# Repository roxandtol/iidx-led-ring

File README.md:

# Rough plans

> [!WARNING]  
> This would be necessary only if you plan on running encrypted or want to make your cab look *really* cool. otherwise, use 🏳️‍⚧️DJ 

So, the iidx lightning cab has enough lights to make a normal person blind, and as we all know, a legacy cab only has a fraction of them, and they're either neons or plain rgb, meanwhile the lightning cab uses mainly the ws2812b led chip for all the rgb stuff (except the turntables and the subwoofer leds, where they use plain rgb).

So to get some of the lightning leds to a legacy cab, we could switch out the neons on the header with some led boards or led strips from aliexpress, since they follow this pattern

In the manual, there's a white tape led section, which we could link the tape leds to the original spotlights the cab has, and 4 argb led sections which correspond to the gray areas on this picture

So we could use some trickery, and try to make some boards to fit in a legacy cab. The solution I was thinking of is this. where the red circles represent a neon, and the green lines represent the sides in a lightning cab. the red circles would have 27 leds each one (since there's 54 per side), and the sides would have 11 leds (to represent the title box leds). This would work for a 1st - 2nd gen cab. Tricoro cabs have a led strip at the top, which would need a simple led strip

Maybe there could be a led board that uses the original holes of a cab, and looks legit enough, and then a diffuser to not make it as bright (although being honest, I think most people will just turn on concentration mode on their cab lol)

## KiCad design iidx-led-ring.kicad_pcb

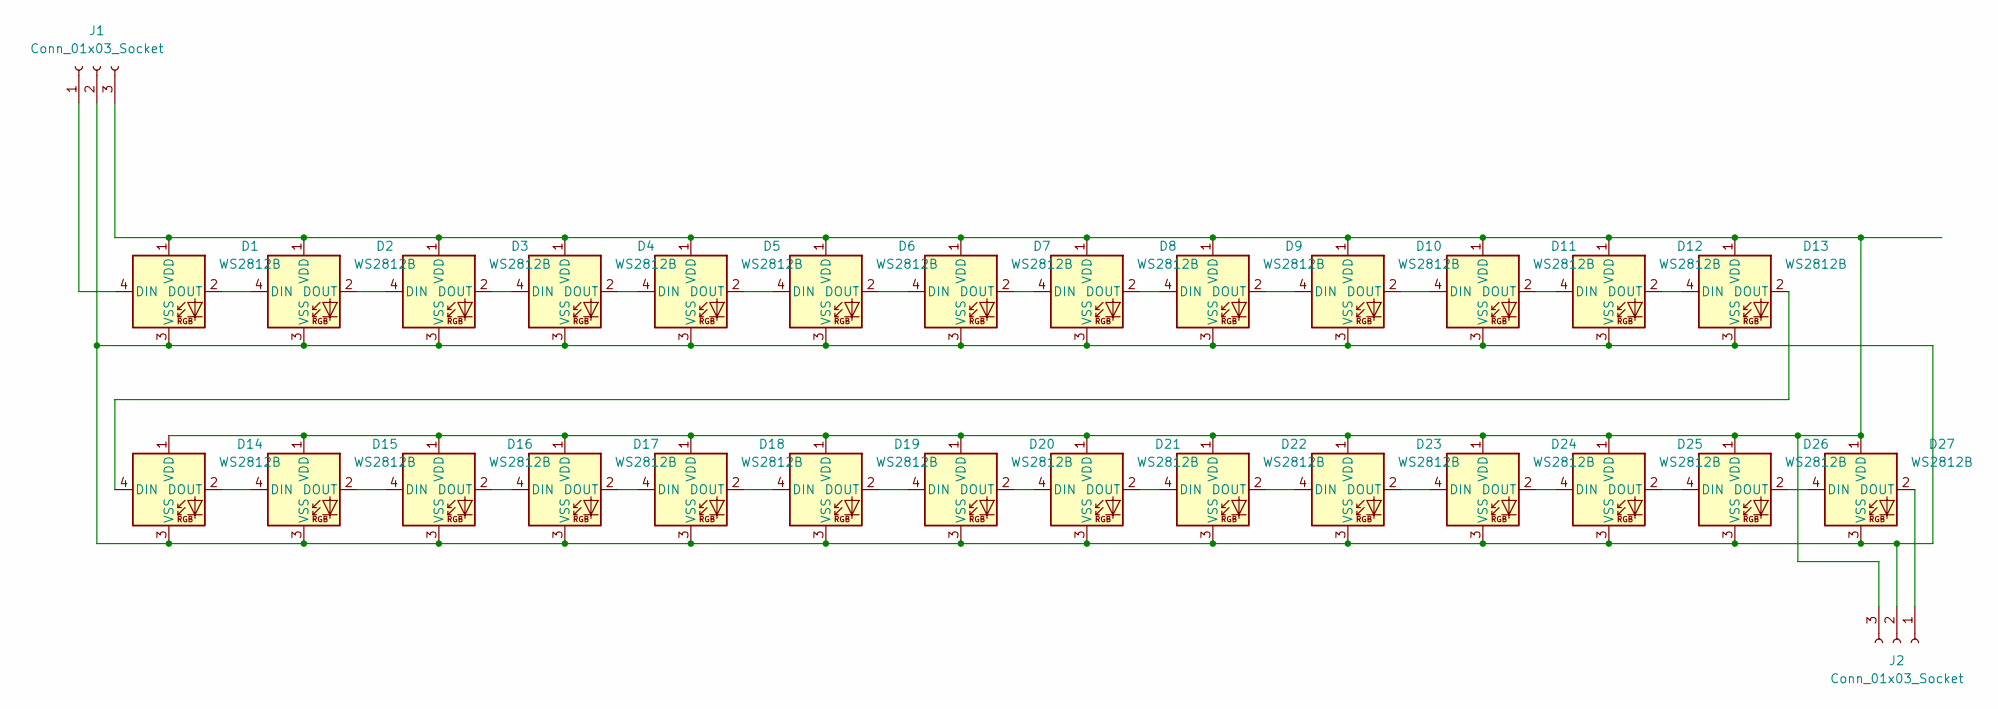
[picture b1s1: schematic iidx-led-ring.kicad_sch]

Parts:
D1, D2, D3, D4, D5, D6, D7, D8, D9, D10, D11, D12, D13, D14, D15, D16, D17, D18, D19, D20, D21, D22, D23, D24, D25, D26, D27: WS2812B; LED_WS2812B_PLCC4_5.0x5.0mm_P3.2mm
J1, J2: Conn_01x03_Socket; JST_PH_B3B-PH-K_1x03_P2.00mm_Vertical

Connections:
unnamed 0: D1.4 (DIN), J1.1; also elsewhere on the board
unnamed: D1.2 (DOUT), D2.4 (DIN)
unnamed 2: D1.1 (VDD), D2.1 (VDD), D3.1 (VDD), D4.1 (VDD), D5.1 (VDD), D6.1 (VDD), D7.1 (VDD), D8.1 (VDD), D9.1 (VDD), D10.1 (VDD), D11.1 (VDD), D12.1 (VDD), D13.1 (VDD), D14.1 (VDD), D15.1 (VDD), D16.1 (VDD), D17.1 (VDD), D18.1 (VDD), D19.1 (VDD), D20.1 (VDD), D21.1 (VDD), D22.1 (VDD), D23.1 (VDD), D24.1 (VDD), D25.1 (VDD), D26.1 (VDD), D27.1 (VDD), J1.3, J2.3; also elsewhere on the board
unnamed 3: D1.3 (VSS), D2.3 (VSS), D3.3 (VSS), D4.3 (VSS), D5.3 (VSS), D6.3 (VSS), D7.3 (VSS), D8.3 (VSS), D9.3 (VSS), D10.3 (VSS), D11.3 (VSS), D12.3 (VSS), D13.3 (VSS), D14.3 (VSS), D15.3 (VSS), D16.3 (VSS), D17.3 (VSS), D18.3 (VSS), D19.3 (VSS), D20.3 (VSS), D21.3 (VSS), D22.3 (VSS), D23.3 (VSS), D24.3 (VSS), D25.3 (VSS), D26.3 (VSS), D27.3 (VSS), J1.2, J2.2; also elsewhere on the board
unnamed: D2.2 (DOUT), D3.4 (DIN)
unnamed: D3.2 (DOUT), D4.4 (DIN)
unnamed: D4.2 (DOUT), D5.4 (DIN)
unnamed: D5.2 (DOUT), D6.4 (DIN)
unnamed: D6.2 (DOUT), D7.4 (DIN)
unnamed: D7.2 (DOUT), D8.4 (DIN)
unnamed: D8.2 (DOUT), D9.4 (DIN)
unnamed: D9.2 (DOUT), D10.4 (DIN)
unnamed: D10.2 (DOUT), D11.4 (DIN)
unnamed: D11.2 (DOUT), D12.4 (DIN)
unnamed: D12.2 (DOUT), D13.4 (DIN)
unnamed: D13.2 (DOUT), D14.4 (DIN)
unnamed: D14.2 (DOUT), D15.4 (DIN)
unnamed: D15.2 (DOUT), D16.4 (DIN)
unnamed: D16.2 (DOUT), D17.4 (DIN)
unnamed: D17.2 (DOUT), D18.4 (DIN)
unnamed: D18.2 (DOUT), D19.4 (DIN)
unnamed: D19.2 (DOUT), D20.4 (DIN)
unnamed: D20.2 (DOUT), D21.4 (DIN)
unnamed: D21.2 (DOUT), D22.4 (DIN)
unnamed: D22.2 (DOUT), D23.4 (DIN)
unnamed: D23.2 (DOUT), D24.4 (DIN)
unnamed: D24.2 (DOUT), D25.4 (DIN)
unnamed: D25.2 (DOUT), D26.4 (DIN)
unnamed: D26.2 (DOUT), D27.4 (DIN)
unnamed 29: D27.2 (DOUT), J2.1; also elsewhere on the board

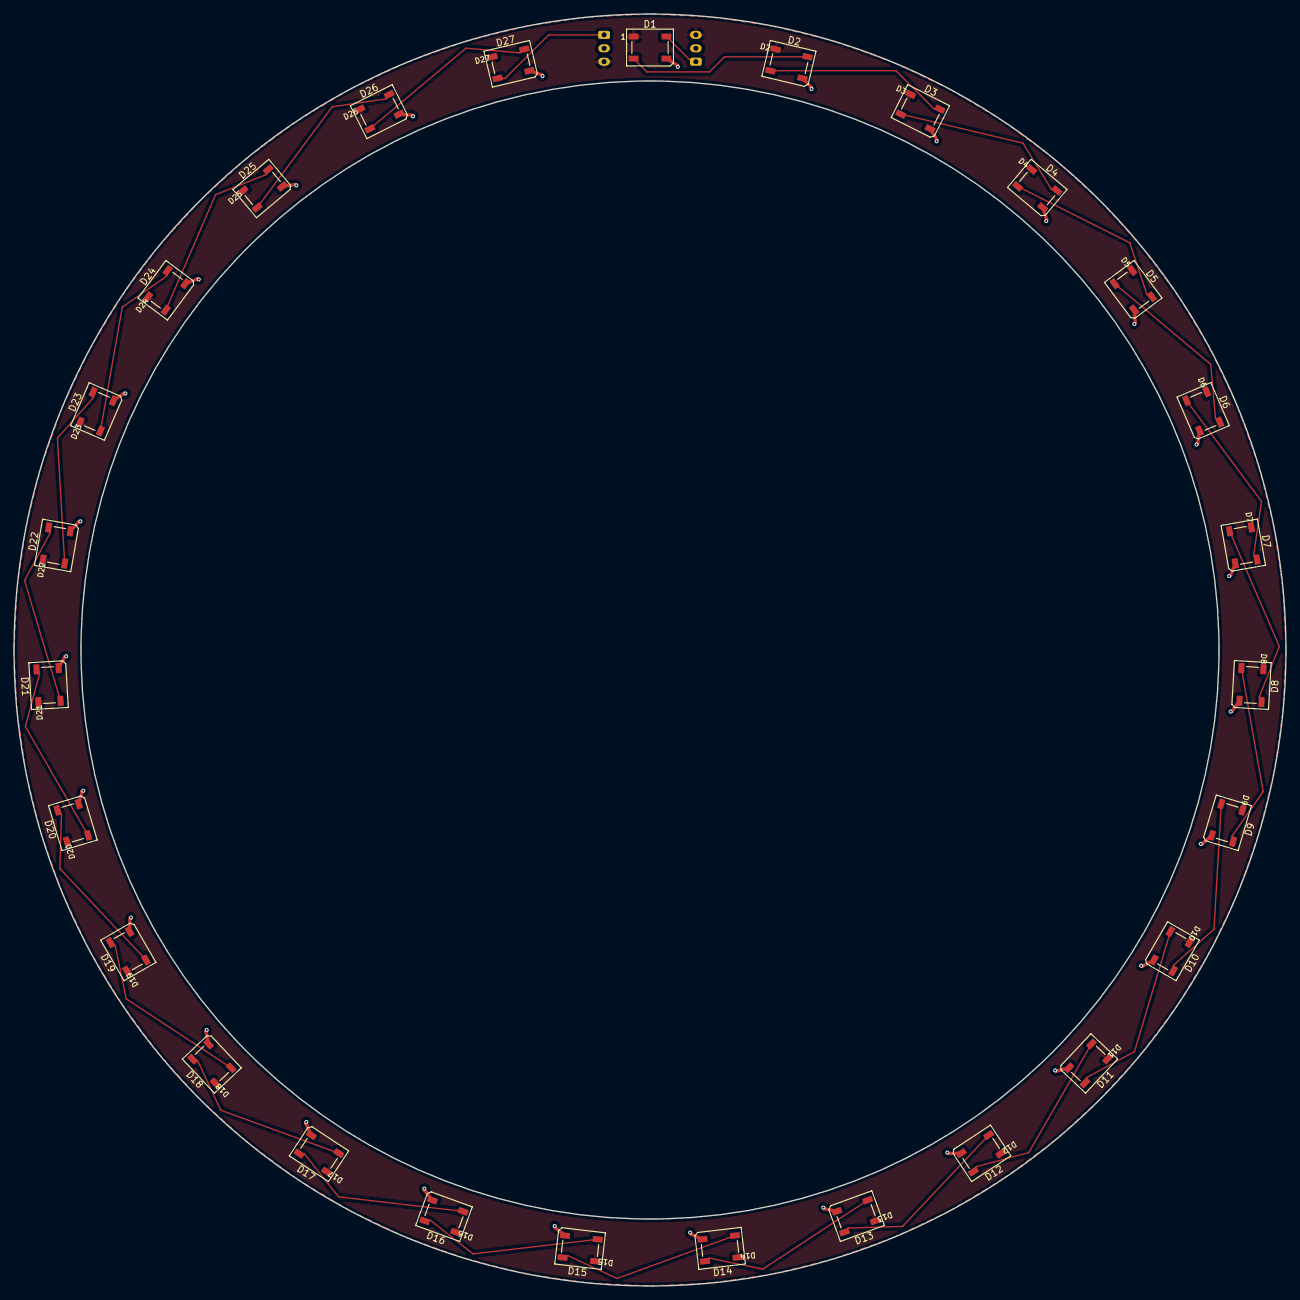
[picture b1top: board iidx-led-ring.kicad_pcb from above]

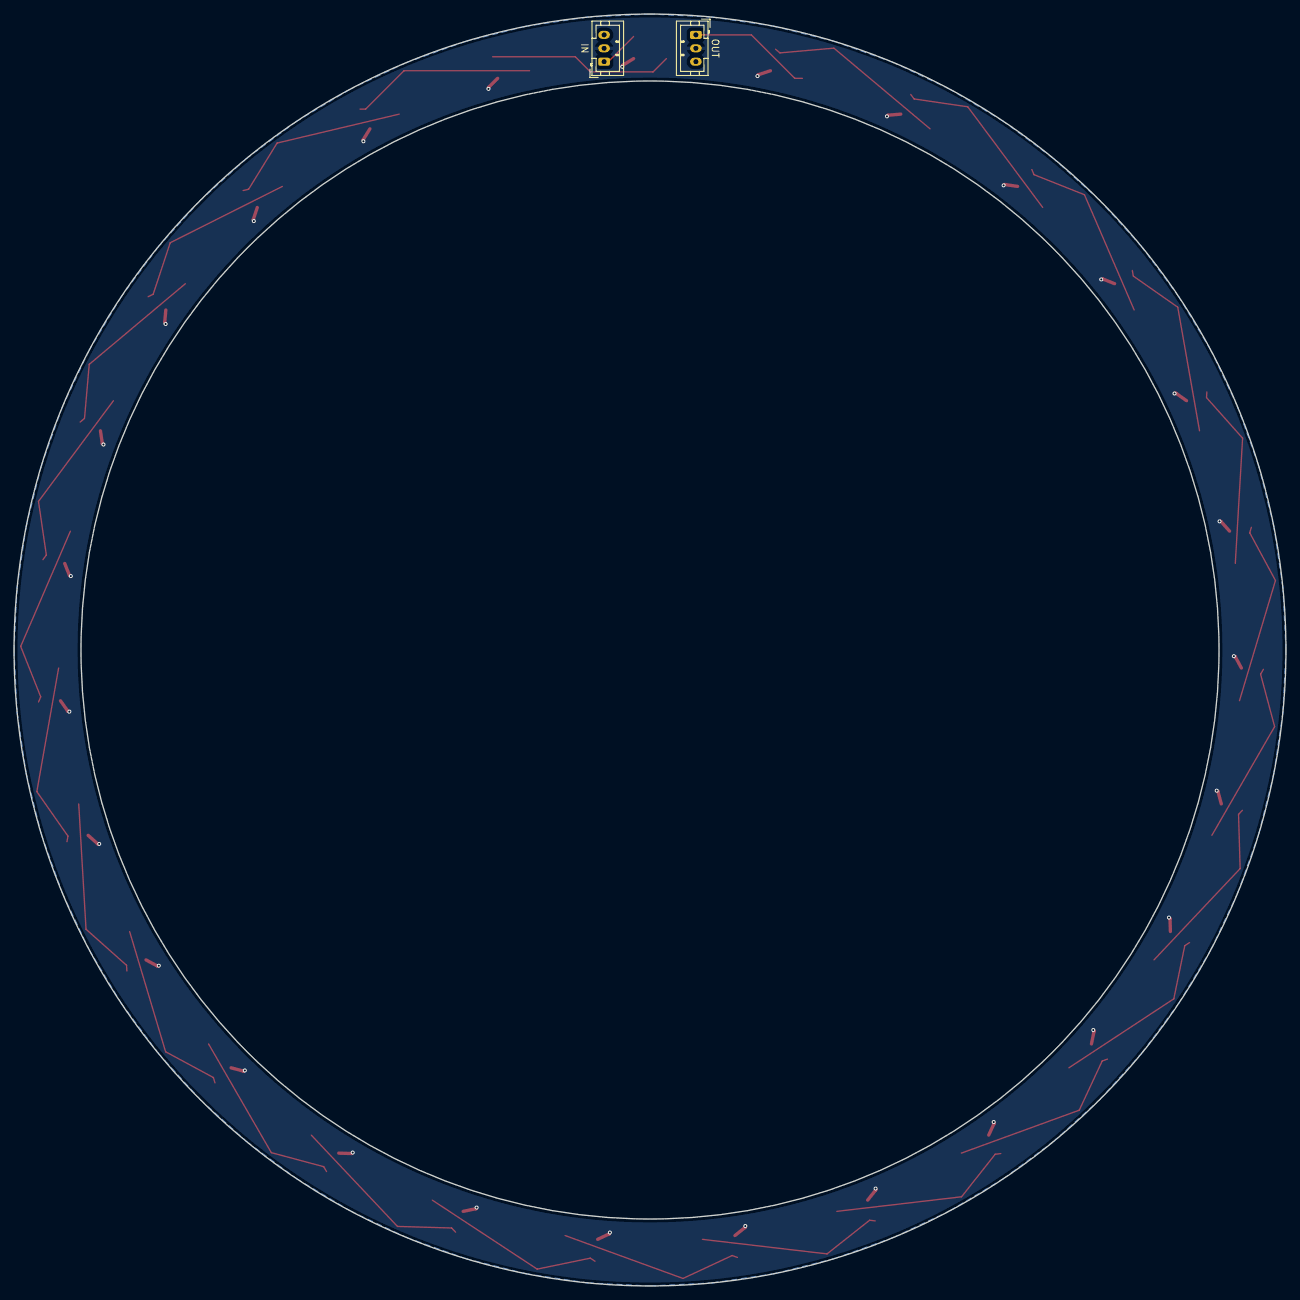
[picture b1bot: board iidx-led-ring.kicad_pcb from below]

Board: 2 copper layers, 190.0 x 190.0 mm, 29 parts (2 on the bottom side), 30 nets.

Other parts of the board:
IN: Conn_01x03_Socket; JST_PH_B3B-PH-K_1x03_P2.00mm_Vertical
OUT: Conn_01x03_Socket; JST_PH_B3B-PH-K_1x03_P2.00mm_Vertical

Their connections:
unnamed 0: IN.1; also elsewhere on the board
unnamed 2: IN.3, OUT.3; also elsewhere on the board
unnamed 3: IN.2, OUT.2; also elsewhere on the board
unnamed 29: OUT.1; also elsewhere on the board

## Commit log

2025-05-28 create project and rough plans
2025-05-28 move rough plans to readme
2025-05-28 finish circular board
2025-05-28 move files inside a folder
2025-08-19 tricoro
